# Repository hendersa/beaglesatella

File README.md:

** SUMMARY **
BeagleSatella is a hardware/software solution that implements the basic 
interface functions of peripherals compatible with the Super Nintendo (SNES)
and Super Famicom (SFC) game consoles. These consoles contain a rarely-used
expansion port on their underside that was intended to interface with a variety
of hardware peripherals. Unfortunately, very few commercial peripherals were 
made available, with the most widely used being the Japan-only Satellaview 
satellite modem. 

BeagleSatella is not emulation, but an actual SNES add-on peripheral that plugs
directly into your game console. BeagleSatella uses a BeagleBone Black (BBB) 
single-board computer with a custom "cape" expansion PCB as the hardware to 
interface with the console. Firmware running on the BBB's pair of programmable
real-time units (PRUs) provides the nanosecond-scale timing required to
interface with the SNES in real-time. Additional peripheral behaviors are 
controlled using kernel drivers and userspace software running under the BBB's
Linux OS. 

** AUTHOR **
Andrew Henderson (hendersa@icculus.org): https://icculus.org/~hendersa

** DESCRIPTION **
The BeagleSatella hardware and firmware offers the following features:

- CPLD-based Hardware filtering and translation of memory-mapped I/O register
accesses from the SNES B-Bus.

- Integrated JTAG interface for easy CPLD reprogramming.

- Arbitrary range of up to 64 contiguous memory-mapped I/O registers available.

- BBB PRU usage guarantees the servicing of register read/write requests within
a 150 ns time window.

- Audio interfacing via the expansion port's stereo audio inputs.

** BUILDING **
Since BeagleSatella has both hardware and software aspects to it, this 
repository is broken down into several subdirectories:

- "cpld" contains the CUPL source code for the CPLD IC used on the cape PCB.

- "firmware" contains the PRU firmware for the BBB that communicates with the
cape PCB.

- "images" contains schematics, board renders, and other images that provide a 
preview of the system.

- "kernel" contains the kernel driver and device tree files for the BBB so that 
the BBB can communicate with the cape PCB.

- "pcb" contains the KiCad design files and gerber files for the cape PCB.

- "userspace" contains BBB userspace software for high-level control of the
whole BeagleSatella system.

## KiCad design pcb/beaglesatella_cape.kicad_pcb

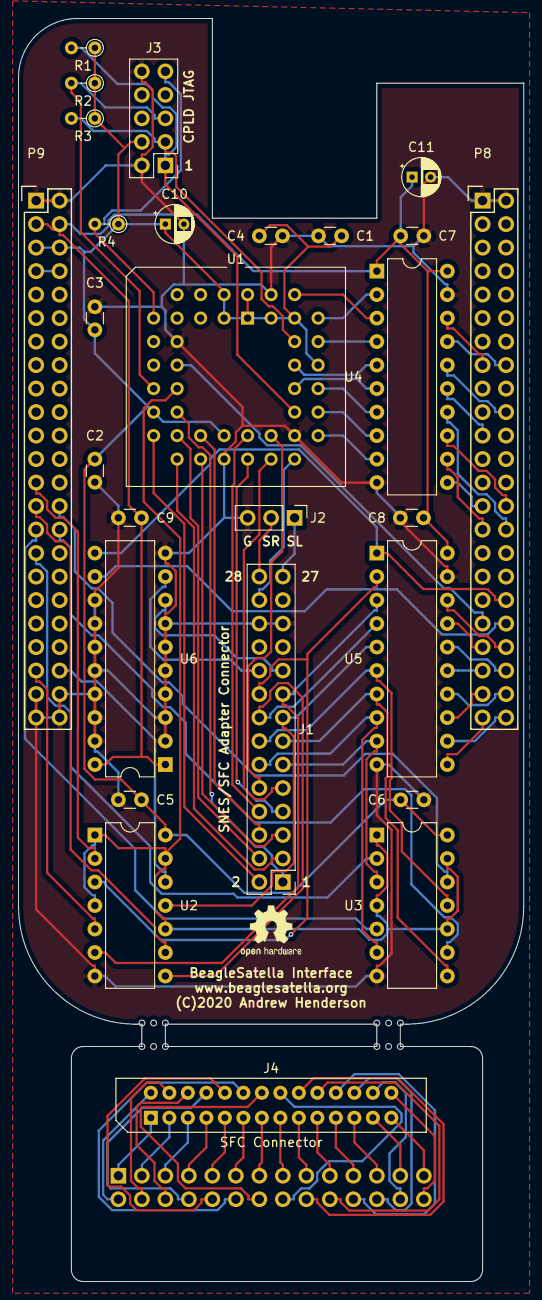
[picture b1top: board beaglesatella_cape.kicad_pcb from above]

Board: 2 copper layers, 54.6 x 136.5 mm, 40 parts (1 on the bottom side), 95 nets.

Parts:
 : Panel_Tab_Hole
 #2,  #3,  #4,  #5,  #6,  #7,  #8,  #9,  #10,  #11,  #12: Panel_Tab_Hole
C1, C2, C3, C4, C5, C6, C7, C8, C9: 0.1uF; C_Disc_D3.0mm_W1.6mm_P2.50mm
C10, C11: 10uF; CP_Radial_D4.0mm_P2.00mm
J1: Conn_02x14_Odd_Even; PinHeader_2x14_P2.54mm_Vertical
J2: AudioConn_01x03_Male; PinHeader_1x03_P2.54mm_Vertical
J3: AVR-JTAG-10; PinHeader_2x05_P2.54mm_Vertical
J4: SFC Connector; Samtec_MECF-40-01-L-DV-WT_2x40_P1.27mm_Polarized_Socket_Hor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
J5: Pin Header; PinHeader_2x14_P2.54mm_Vertical
P8, P9: BeagleBone_Black_Header; Socket_BeagleBone_Black
R1, R2, R3, R4: 10K; R_Axial_DIN0204_L3.6mm_D1.6mm_P2.54mm_Vertical
U1: ATF1504AS-10JU44; PLCC-44_THT-Socket
U2, U3: 74AHCT125; DIP-14_W7.62mm
U4, U5, U6: 74LVC245AN; DIP-20_W7.62mm

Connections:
+3V3: C7.2, C8.2, C9.2, C11.1, P9.3, P9.4, U4.1, U4.20, U5.20, U6.1, U6.20
+5V: C1.1, C2.1, C3.1, C4.1, C5.2, C6.2, C10.1, J3.4, P9.5, P9.6, R1.1, R2.1, R3.1, R4.1, U1.1, U1.2, U1.3, U1.15, U1.23, U1.35, U1.41, U1.43, U1.44, U2.14, U3.14
/D0: J1.11, U3.3, U5.9
/D0_3V: P8.45, U5.11
/D0_IN_3V: P9.31, U3.2
/D1: J1.12, U3.6, U5.8
/D1_3V: P8.46, U5.12
/D1_IN_3V: P9.29, U3.5
/D2: J1.13, U3.8, U5.7
/D2_3V: P8.43, U5.13
/D2_IN_3V: P9.30, U3.9
/D3: J1.14, U3.11, U5.6
/D3_3V: P8.44, U5.14
/D3_IN_3V: P9.28, U3.12
/D4: J1.15, U2.11, U5.5
/D4_3V: P8.41, U5.15
/D4_IN_3V: P9.42, U2.12
/D5: J1.16, U2.8, U5.4
/D5_3V: P8.42, U5.16
/D5_IN_3V: P9.27, U2.9
/D6: J1.17, U2.6, U5.3
/D6_3V: P8.39, U5.17
/D6_IN_3V: P9.41, U2.5
/D7: J1.18, U2.3, U5.2
/D7_3V: P8.40, U5.18
/D7_IN_3V: P9.25, U2.2
/PA0: J1.1, U1.16
/PA0_3V: P8.27, U4.11
/PA0_5V: U1.29, U4.9
/PA1: J1.2, U1.17
/PA1_3V: P8.29, U4.12
/PA1_5V: U1.31, U4.8
/PA2: J1.3, U1.18
/PA2_3V: P8.28, U4.13
/PA2_5V: U1.33, U4.7
/PA3: J1.4, U1.19
/PA3_3V: P8.30, U4.14
/PA3_5V: U1.34, U4.6
/PA4: J1.5, U1.20
/PA4_3V: P8.21, U4.15
/PA4_5V: U1.36, U4.5
/PA5: J1.6, U1.21
/PA5_3V: P8.20, U4.16
/PA5_5V: U1.37, U4.4
/PA6: J1.7, U1.24
/PA7: J1.8, U1.25
/PIN1: J4.1, J5.1
/PIN3: J4.3, J5.3
/PIN5: J4.5, J5.5
/PIN7: J4.7, J5.7
/PIN9: J4.9, J5.9
/PIN11: J4.11, J5.11
/PIN13: J4.13, J5.13
/PIN15: J4.15, J5.15
/PIN17: J4.17, J5.17
/PIN19: J4.19, J5.19
/PIN21: J4.21, J5.21
/PIN23: J4.23, J5.23
/PIN25: J4.25, J5.25
/PIN27: J4.27, J5.27
/~PARD: J1.10, U1.27
/~PARD_3V: P8.16, U4.17
/~PARD_5V: U1.40, U4.3
/~PAWR: J1.9, U1.26
/~PAWR_3V: P8.15, U4.18
/~PAWR_5V: U1.39, U4.2
GNDD: C1.2, C2.2, C3.2, C4.2, C5.1, C6.1, C7.1, C8.1, C9.1, C10.2, C11.2, J1.23, J1.24, J2.3, J3.2, J3.10, P8.1, P8.2, P9.1, P9.2, P9.43, P9.44, P9.45, P9.46, U1.10, U1.22, U1.30, U1.42, U2.7, U3.7, U4.10, U4.19, U5.10, U5.19, U6.2, U6.3, U6.4, U6.5, U6.6, U6.7, U6.10, U6.13, U6.14, U6.15, U6.16, U6.17, U6.18, U6.19
unnamed: J3.1, R1.2, U1.32
unnamed: J3.3, R3.2, U1.38
unnamed: J3.5, R2.2, U1.13
unnamed: J3.9, R4.2, U1.7
unnamed: J4.2, J5.2
unnamed: J4.4, J5.4
unnamed: J4.6, J5.6
unnamed: J4.8, J5.8
unnamed: J4.10, J5.10
unnamed: J4.12, J5.12
unnamed: J4.14, J5.14
unnamed: J4.16, J5.16
unnamed: J4.18, J5.18
unnamed: J4.20, J5.20
unnamed: J4.22, J5.22
unnamed: J4.24, J5.24
unnamed: J4.26, J5.26
unnamed: J4.28, J5.28
SFC_VCC: J1.20, U6.9
SFC_VCC_3V: P8.36, U5.1, U6.11
SL: J1.27, J2.1
SR: J1.28, J2.2
SYS_5V: P9.7, P9.8
~DATA_OE: U1.14, U2.1, U2.4, U2.10, U2.13, U3.1, U3.4, U3.10, U3.13
~IRQ: J1.26, U1.28
~IRQ_3V: P8.37, U1.12
~RESET: J1.19, U6.8
~RESET_3V: P8.38, U6.12

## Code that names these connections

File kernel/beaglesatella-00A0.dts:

/*
 * Copyright (C) 2020 Andrew Henderson (hendersa@icculus.org)
 *
 * This program is free software; you can redistribute it and/or modify
 * it under the terms of the GNU General Public License version 2 as
 * published by the Free Software Foundation.
 */
/dts-v1/;
/plugin/;

/ {
	compatible = "ti,beaglebone-black";

	/* identification */
	part-number = "BEAGLESATELLA";
	version = "00A0";

	fragment@0 {
		target-path="/";
		__overlay__ {
			pru-beaglesatella {
				compatible = "beaglesatella,beaglesatella";
				pruss = <&pruss>;
				interrupt-parent = <&pruss_intc>;
				interrupts = <22>, <23>, <24>;
				interrupt-names = "from_bl_1", "to_bl", "from_bl_2";
			};
		};
	};

	/*
	 * Free up the pins used by the cape from the pinmux helpers.
	 */
	fragment@1 {
		target = <&ocp>;
		__overlay__ {

			/* PRU0 R30 DataOut[7:0] pins (Mode 5, Output) */
			P9_31_pinmux { status = "disabled"; };  /* P9_31:   R30[0] -> DataOut[0] */
			P9_29_pinmux { status = "disabled"; };  /* P9_29:   R30[1] -> DataOut[1] */ 
			P9_30_pinmux { status = "disabled"; };  /* P9_30:   R30[2] -> DataOut[2] */
			P9_28_pinmux { status = "disabled"; };  /* P9_28:   R30[3] -> DataOut[3] */
			P9_92_pinmux { status = "disabled"; };	/* P9_42.1: R30[4] -> DataOut[4] */
			P9_27_pinmux { status = "disabled"; };	/* P9_27:   R30[5] -> DataOut[5] */
			P9_91_pinmux { status = "disabled"; };  /* P9_41.1: R30[6] -> DataOut[6] */
			P9_25_pinmux { status = "disabled"; };	/* P9_25:   R30[7] -> DataOut[7] */

			/* Eliminate P9_41/42 conflicts (Mode 7, Input) */
			P9_41_pinmux { status = "disabled"; };
			P9_42_pinmux { status = "disabled"; };

			/* PRU0 R31 PARD input pin (Mode 6, Input) */
			P8_16_pinmux { status = "disabled"; };	/* P8_16: PARD -> R31[14] */

			/* PRU0 R31 PAWR input pin (Mode 6, Input) */
			P8_15_pinmux { status = "disabled"; };	/* P8_15: PAWR -> R31[15] */

			/* PRU1 R31 DataIn[7:0] pins (Mode 6, Input) */
			P8_45_pinmux { status = "disabled"; };	/* P8_45: DataIn[0] -> R31[0] */
			P8_46_pinmux { status = "disabled"; };	/* P8_46: DataIn[1] -> R31[1] */
			P8_43_pinmux { status = "disabled"; };	/* P8_43: DataIn[2] -> R31[2] */
			P8_44_pinmux { status = "disabled"; };	/* P8_44: DataIn[3] -> R31[3] */
			P8_41_pinmux { status = "disabled"; };	/* P8_41: DataIn[4] -> R31[4] */
			P8_42_pinmux { status = "disabled"; };	/* P8_42: DataIn[5] -> R31[5] */
			P8_39_pinmux { status = "disabled"; };	/* P8_39: DataIn[6] -> R31[6] */
			P8_40_pinmux { status = "disabled"; };  /* P8_40: DataIn[7] -> R31[7] */

			/* PRU1 R31 AddrIn[5:0] pins (Mode 6, Input) */
			P8_27_pinmux { status = "disabled"; };  /* P8_27: AddrIn[0] -> R31[8] */
			P8_29_pinmux { status = "disabled"; };  /* P8_29: AddrIn[1] -> R31[9] */
			P8_28_pinmux { status = "disabled"; };  /* P8_28: AddrIn[2] -> R31[10] */
			P8_30_pinmux { status = "disabled"; };  /* P8_30: AddrIn[3] -> R31[11] */
			P8_21_pinmux { status = "disabled"; };  /* P8_21: AddrIn[4] -> R31[12] */
			P8_20_pinmux { status = "disabled"; };	/* P8_20: AddrIn[5] -> R31[13] */

			/* KERNEL GPIO /RESET pin (Mode 7, Input) */
			P8_38_pinmux { status = "disabled"; };  /* P8_38: /RESET -> GPIO2[15] */

			/* KERNEL GPIO /IRQ pin (Mode 7, Output) */
			P8_37_pinmux { status = "disabled"; };  /* P8_37: GPIO2[14] -> /IRQ */

			/* KERNEL GPIO VCC pin (Mode 7, Input) */
			P8_36_pinmux { status = "disabled"; };	/* P8_36: VCC -> GPIO2[16] */

			beaglesatella_helper: helper {
				compatible = "bone-pinmux-helper";
				pinctrl-names = "default";
				pinctrl-0 = <&beaglesatella_pins>;
				status = "okay";
			};
		};
	};

	fragment@2 {
		target = <&am33xx_pinmux>;
		__overlay__ {
			beaglesatella_pins: beaglesatella_pins {
				pinctrl-single,pins = <
					/* PRU0 R30 DataOut_3V[7:0] pins (Mode 5: PRU Output) */
					0x190 0x25	/* P9_31 */
					0x194 0x25	/* P9_29 */
					0x198 0x25	/* P9_30 */
					0x19c 0x25	/* P9_28 */
					0x1a0 0x25	/* P9_42.1 */
					0x1a4 0x25	/* P9_27 */
					0x1a8 0x25	/* P9_41.1 */
					0x1ac 0x25	/* P9_25 */

					/* Eliminate P9_41/42 conflicts (Mode 7: GPIO, Input, Disabled Pull-Up/Down, Fast Slew: 0x2F) */
					0x1b4 0x2F	/* P9_41 */
					0x164 0x2F	/* P9_42 */

					/* PRU0 R31 /PARD_3V pin (Mode 6: PRU Input) */
					0x038 0x26	/* P8_16 */

					/* PRU0 R31 /PAWR_3V pin (Mode 6: PRU Input) */
					0x03c 0x26	/* P8_15 */

					/* PRU1 R31 DataIn_3V[7:0] pins (Mode 6: PRU Input) */
					0x0a0 0x26	/* P8_45 */
					0x0a4 0x26	/* P8_46 */
					0x0a8 0x26	/* P8_43 */
					0x0ac 0x26	/* P8_44 */
					0x0b0 0x26	/* P8_41 */
					0x0b4 0x26	/* P8_42 */
					0x0b8 0x26	/* P8_39 */
					0x0bc 0x26	/* P8_40 */

					/* PRU1 R31 AddrIn[5:0] pins (Mode 6: PRU Input) */
					0x0e0 0x26	/* P8_27 */
					0x0e4 0x26	/* P8_29 */
					0x0e8 0x26	/* P8_28 */
					0x0ec 0x26	/* P8_30 */
					0x080 0x26	/* P8_21 */
					0x084 0x26	/* P8_20 */

					/* KERNEL GPIO /RESET_3V pin (Mode 7: GPIO, Input, Pull Up, Fast Slew: 0x37) */
					0x0c4 0x37	/* P8_38 */ 

					/* KERNEL GPIO /IRQ_3V pin (Mode 7: GPIO, Output, Disabled Pull Up/Down, Fast Slew: 0x0F) */
					0x0c0 0x0F	/* P8_37 */ 

					/* KERNEL GPIO SFC_VCC_3V pin (Mode 7: GPIO, Input, Pull Down, Fast Slew: 0x27) */
					0x0c8 0x27	/* P8_36 */

				>;
			};
		};
	};

};

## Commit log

2020-06-19 Initial commit of work done to date
